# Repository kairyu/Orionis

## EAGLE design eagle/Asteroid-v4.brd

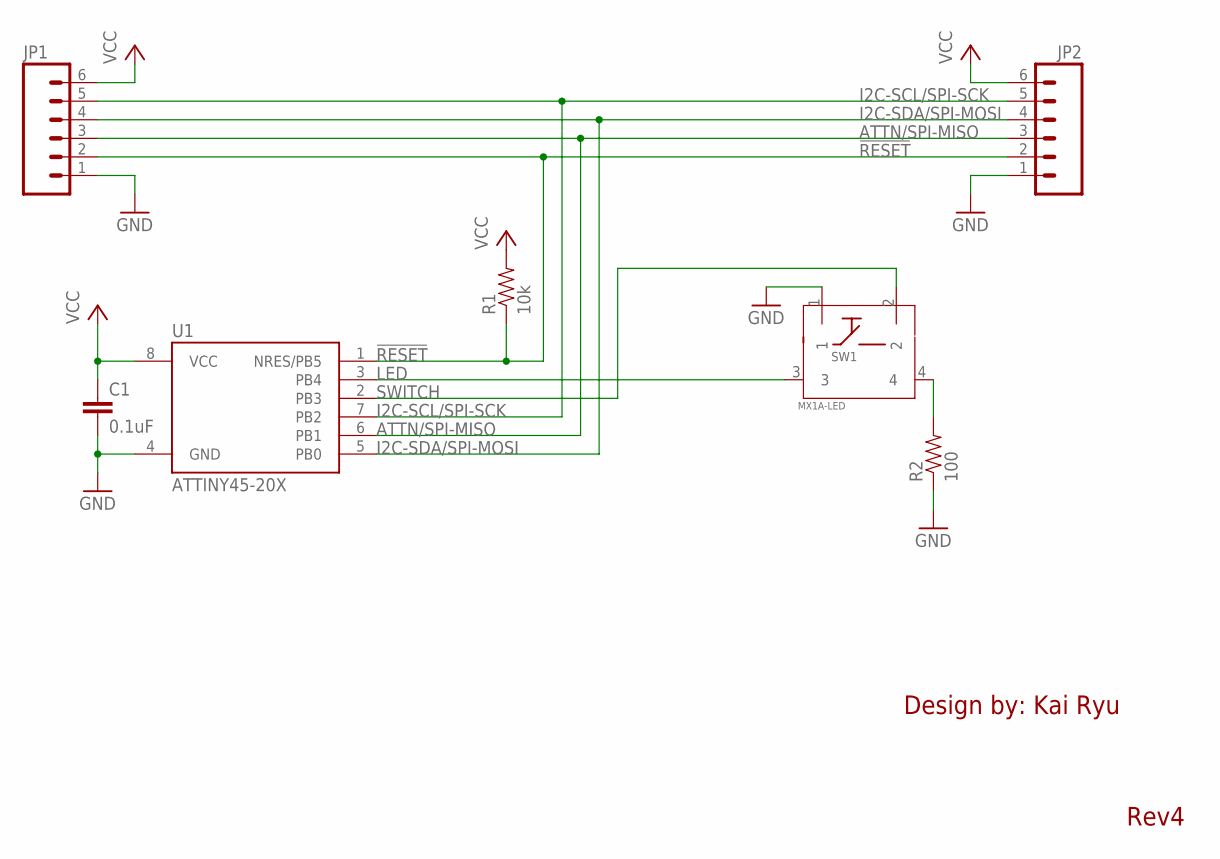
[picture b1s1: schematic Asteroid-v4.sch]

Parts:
C1: 0.1uF; 0603-CAP
JP1, JP2: 1X06
R1: 10k; 0603-RES
R2: 100; 0603-RES
SW1: MX1A-LED
U1: ATTINY45-20X; TSSOP8_4MM4

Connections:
!RESET!: JP1.2, JP2.2, R1.1, U1.1 (NRES/PB5)
ATTN/SPI-MISO: JP1.3, JP2.3, U1.6 (PB1)
GND: C1.2, JP1.1, JP2.1, R2.1, SW1.1, U1.4 (GND)
I2C-SCL/SPI-SCK: JP1.5, JP2.5, U1.7 (PB2)
I2C-SDA/SPI-MOSI: JP1.4, JP2.4, U1.5 (PB0)
LED: SW1.3, U1.3 (PB4)
unnamed: R2.2, SW1.4
SWITCH: SW1.2, U1.2 (PB3)
VCC: C1.1, JP1.6, JP2.6, R1.2, U1.8 (VCC)

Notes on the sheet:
Design by: Kai Ryu
Rev4

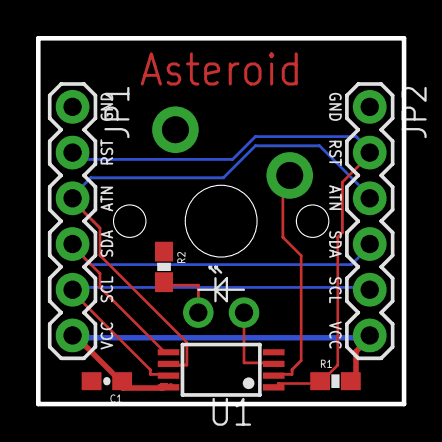
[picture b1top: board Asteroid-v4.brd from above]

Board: 2 copper layers, 20.3 x 20.3 mm, 7 parts (1 on the bottom side), 9 nets.

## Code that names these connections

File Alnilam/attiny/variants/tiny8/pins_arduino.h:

/*
  pins_arduino.c - pin definitions for the Arduino board
  Part of Arduino / Wiring Lite

  Copyright (c) 2005 David A. Mellis

  This library is free software; you can redistribute it and/or
  modify it under the terms of the GNU Lesser General Public
  License as published by the Free Software Foundation; either
  version 2.1 of the License, or (at your option) any later version.

  This library is distributed in the hope that it will be useful,
  but WITHOUT ANY WARRANTY; without even the implied warranty of
  MERCHANTABILITY or FITNESS FOR A PARTICULAR PURPOSE.  See the GNU
  Lesser General Public License for more details.

  You should have received a copy of the GNU Lesser General
  Public License along with this library; if not, write to the
  Free Software Foundation, Inc., 59 Temple Place, Suite 330,
  Boston, MA  02111-1307  USA

  $Id: pins_arduino.c 565 2009-03-25 10:50:00Z dmellis $

  Modified 28-08-2009 for attiny84 R.Wiersma
  Modified 09-10-2009 for attiny45 A.Saporetti
*/

#ifndef Pins_Arduino_h
#define Pins_Arduino_h

#include <avr/pgmspace.h>

// ATMEL ATTINY45 / ARDUINO
//
//                  +-\/-+
// Ain0 (D 5) PB5  1|    |8  Vcc
// Ain3 (D 3) PB3  2|    |7  PB2 (D 2)  Ain1
// Ain2 (D 4) PB4  3|    |6  PB1 (D 1) pwm1
//            GND  4|    |5  PB0 (D 0) pwm0
//                  +----+

static const uint8_t A0 = 6;
static const uint8_t A1 = 7;
static const uint8_t A2 = 8;
static const uint8_t A3 = 9;

#define digitalPinToPCICR(p)    ( ((p) >= 0 && (p) <= 4) ? (&GIMSK) : ((uint8_t *)0) )
#define digitalPinToPCICRbit(p) ( PCIE )
#define digitalPinToPCMSK(p)    ( ((p) <= 4) ? (&PCMSK) : ((uint8_t *)0) )
#define digitalPinToPCMSKbit(p) ( (p) )

#define analogPinToChannel(p)   ( (p) < 6 ? (p) : (p) - 6 )

#ifdef ARDUINO_MAIN

// these arrays map port names (e.g. port B) to the
// appropriate addresses for various functions (e.g. reading
// and writing) tiny45 only port B 
const uint16_t PROGMEM port_to_mode_PGM[] = {
	NOT_A_PORT,
	NOT_A_PORT,
	(uint16_t) &DDRB,
};

const uint16_t PROGMEM port_to_output_PGM[] = {
	NOT_A_PORT,
	NOT_A_PORT,
	(uint16_t) &PORTB,
};

const uint16_t PROGMEM port_to_input_PGM[] = {
	NOT_A_PIN,
	NOT_A_PIN,
	(uint16_t) &PINB,
};

const uint8_t PROGMEM digital_pin_to_port_PGM[] = {
	PB, /* 0 */
	PB,
	PB,
	PB,
	PB, 
	PB, // 5
	PB, // A0
	PB,
	PB,
	PB, // A4

};

const uint8_t PROGMEM digital_pin_to_bit_mask_PGM[] = {
	_BV(0), /* 0, port B */
	_BV(1),
	_BV(2),
	_BV(3), /* 3 port B */
	_BV(4),
	_BV(5),
	_BV(5),
	_BV(2),
	_BV(4),
	_BV(3),
};

const uint8_t PROGMEM digital_pin_to_timer_PGM[] = {
	TIMER0A, /* OC0A */
	TIMER0B,
	NOT_ON_TIMER,
	TIMER1B,
	NOT_ON_TIMER,
	NOT_ON_TIMER,
	NOT_ON_TIMER,
	NOT_ON_TIMER,
	TIMER1B,
	NOT_ON_TIMER,
};

#endif

#endif

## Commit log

2013-03-22 Imports files.
2013-03-22 Supports CLI compiling.
2013-03-22 Imports prototype board EAGLE files.
2013-04-25 Modify makefile to support cygwin.
2013-04-25 Change to use new arduino-tiny core.
2013-04-25 Change to use new core and support uploading via command line.
2013-04-25 Support uploading via command line.
2013-04-25 Fix i2c communication bugs. Add features: fade mode, fade once mode, smooth change.
2013-04-25 Add modified ArduinoISP into repo.
2013-04-25 Fix reset issue. Add some codes for demo feature.
2013-04-25 Update .gitignore to ignore *.swp file made by vim.

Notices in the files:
parts and their libraries:
SparkFun-Passives: Licensing: CC v3.0 Share-Alike You are welcome to use this library for commercial purposes.
